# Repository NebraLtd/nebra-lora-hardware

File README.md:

# nebra-lora-hardware
Hardware Files for a variety of Nebra Lora Hardware

# Licenses

All hardware is licensed under Creative Commons Attribution Share Alike 4.0.

Software Snippets are licensed under the MIT License.

Copies of both can be found in the respective HARDWARE-LICENSE and SOFTWARE-LICENSE files.

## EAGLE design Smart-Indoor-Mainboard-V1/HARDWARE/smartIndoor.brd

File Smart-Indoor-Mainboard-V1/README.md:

# Nebra Smart Indoor Mainboard
Hardware Files for the mainboard used in the Nebra Helium Indoor Hotspot

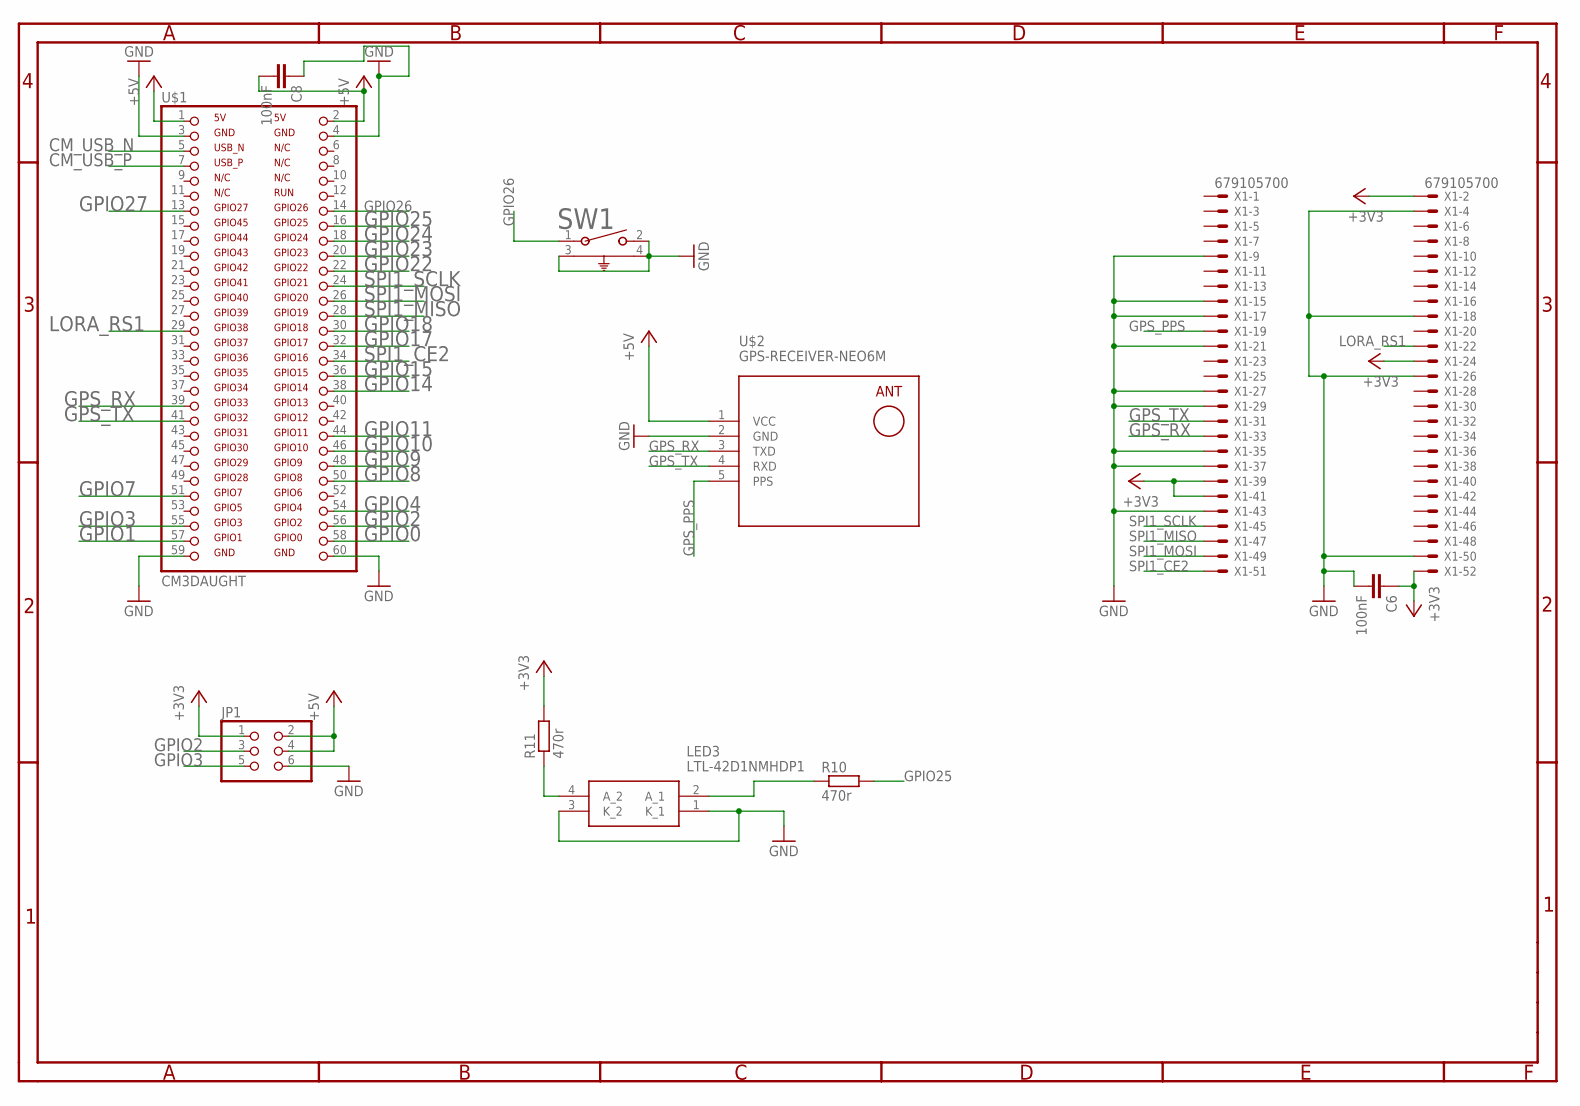
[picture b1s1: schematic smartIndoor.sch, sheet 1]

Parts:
C6, C8: 100nF; C0603
JP1: PINHD-2X3; 2X03
LED3: LTL-42D1NMHDP1; LTL42D1NMHDP1
R10, R11: 470r; R0603
SW1: 1825027-8; SW2_1825027-C_TEC
U$1: CM3DAUGHT; 2X30
U$2: GPS-RECEIVER-NEO6M
X1: 679105700

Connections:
+3V3: C6.1, JP1.1, R11.2, X1.2, X1.24, X1.39, X1.41, X1.52; also elsewhere on the board
+5V: C8.2, JP1.2, JP1.4, U$1.1 (5V), U$1.2 (5V), U$2.1 (VCC); also elsewhere on the board
CM_USB_N: U$1.5 (USB_N); also elsewhere on the board
CM_USB_P: U$1.7 (USB_P); also elsewhere on the board
GND: C6.2, C8.1, JP1.6, LED3.1 (K_1), LED3.3 (K_2), SW1.2, SW1.3, SW1.4, U$1.3 (GND), U$1.4 (GND), U$1.59 (GND), U$1.60 (GND), U$2.2 (GND), X1.4, X1.9, X1.15, X1.17, X1.18, X1.21, X1.26, X1.27, X1.29, X1.35, X1.37, X1.43, X1.50; also elsewhere on the board
GPIO0: U$1.58 (GPIO0)
GPIO1: U$1.57 (GPIO1)
GPIO2: JP1.3, U$1.56 (GPIO2)
GPIO3: JP1.5, U$1.55 (GPIO3)
GPIO4: U$1.54 (GPIO4)
GPIO7: U$1.51 (GPIO7)
GPIO8: U$1.50 (GPIO8)
GPIO9: U$1.48 (GPIO9)
GPIO10: U$1.46 (GPIO10)
GPIO11: U$1.44 (GPIO11)
GPIO14: U$1.38 (GPIO14)
GPIO15: U$1.36 (GPIO15)
GPIO17: U$1.32 (GPIO17)
GPIO18: U$1.30 (GPIO18)
GPIO22: U$1.22 (GPIO22)
GPIO23: U$1.20 (GPIO23)
GPIO24: U$1.18 (GPIO24)
GPIO25: R10.2, U$1.16 (GPIO25)
GPIO26: SW1.1, U$1.14 (GPIO26)
GPIO27: U$1.13 (GPIO27)
GPS_PPS: U$2.5 (PPS), X1.19
GPS_RX: U$1.39 (GPIO33), U$2.3 (TXD), X1.33
GPS_TX: U$1.41 (GPIO32), U$2.4 (RXD), X1.31
LORA_RS1: U$1.29 (GPIO38), X1.22
unnamed: LED3.4 (A_2), R11.1
unnamed: LED3.2 (A_1), R10.1
SPI1_CE2: U$1.34 (GPIO16), X1.51
SPI1_MISO: U$1.28 (GPIO19), X1.47
SPI1_MOSI: U$1.26 (GPIO20), X1.49
SPI1_SCLK: U$1.24 (GPIO21), X1.45

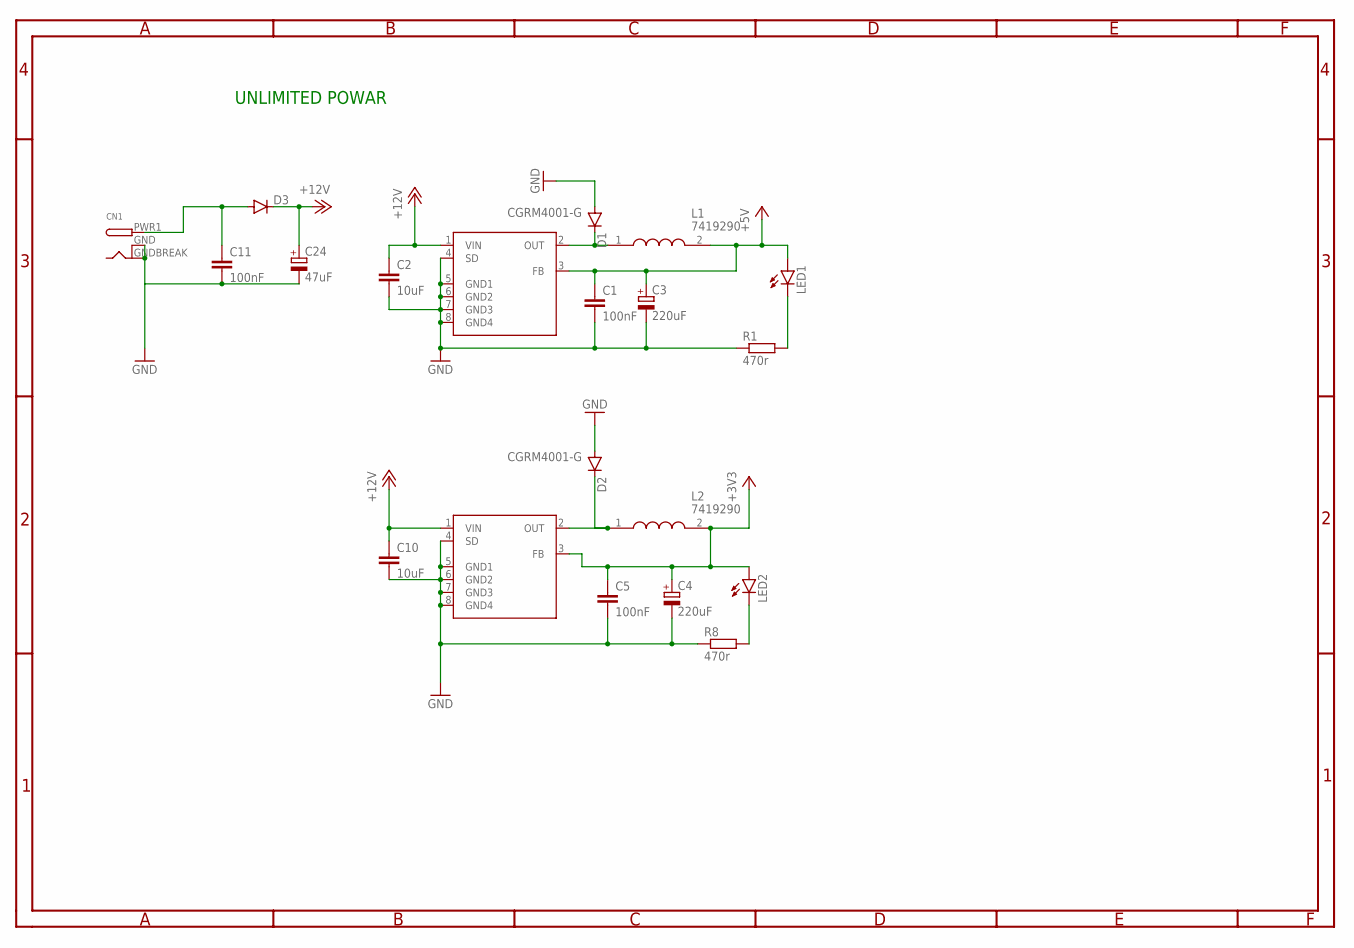
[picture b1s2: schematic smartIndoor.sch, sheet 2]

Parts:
C1, C5, C11: 100nF; C0603
C2, C10: 10uF; C0603
C3, C4: 220uF; PANASONIC_D
C24: 47uF; PANASONIC_D
CN1: DCBARRELSMT; DCJACK_2MM_SMT
D1, D2: CGRM4001-G; SOD-123_MINI-SMA
D3: DIODE-SMB; SMB
L1, L2: 7419290; INDPM115100X410N
LED1, LED2: LEDCHIP-LED0603; CHIP-LED0603
R1, R8: 470r; R0603
U1, U2: AP1509; SO08

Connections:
+3V3: C4.+, C5.1, L2.2, LED2.A, U2.3 (FB); also elsewhere on the board
+5V: C1.1, C3.+, L1.2, LED1.A, U1.3 (FB); also elsewhere on the board
+12V: C2.1, C10.1, C24.+, D3.C, U1.1 (VIN), U2.1 (VIN)
GND: C1.2, C2.2, C3.-, C4.-, C5.2, C10.2, C11.2, C24.-, CN1.GND (GNDBREAK), CN1.GNDBREAK (GND), D1.A, D2.A, R1.1, R8.1, U1.4 (SD), U1.5 (GND1), U1.6 (GND2), U1.7 (GND3), U1.8 (GND4), U2.4 (SD), U2.5 (GND1), U2.6 (GND2), U2.7 (GND3), U2.8 (GND4); also elsewhere on the board
unnamed: C11.1, CN1.PWR1 (PWR), D3.A
unnamed: LED1.C, R1.2
unnamed: D1.C, L1.1, U1.2 (OUT)
unnamed: LED2.C, R8.2
unnamed: D2.C, L2.1, U2.2 (OUT)

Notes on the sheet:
UNLIMITED POWAR

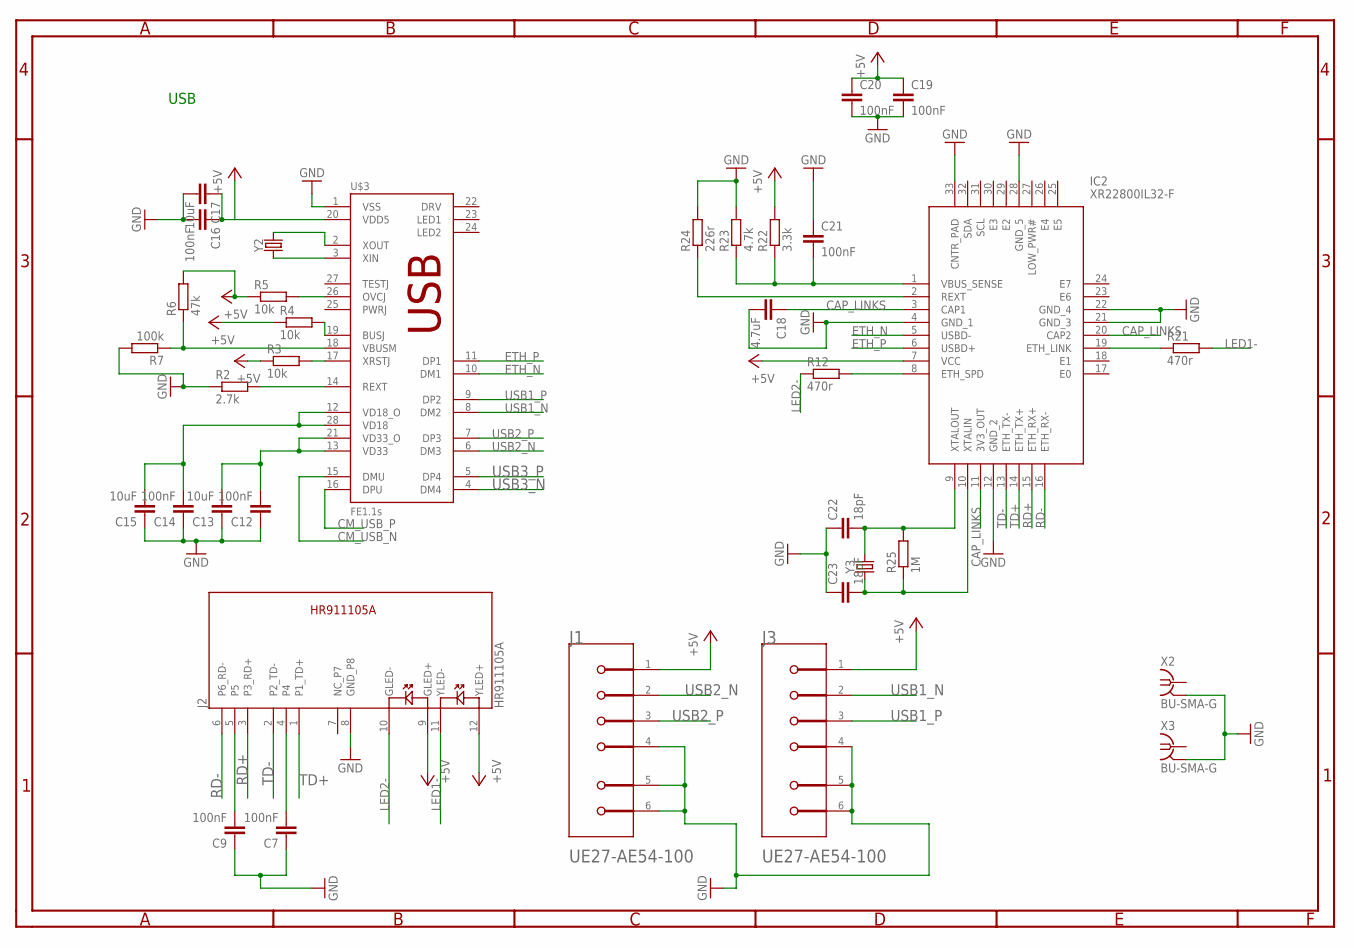
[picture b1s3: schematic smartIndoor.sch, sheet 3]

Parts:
C7, C9, C12, C14, C16, C19, C20, C21: 100nF; C0603
C13, C15, C17: 10uF; C0603
C18: 4.7uF; C0603
C22, C23: 18pF; C0603
IC2: XR22800IL32-F; QFN50P500X500X100-33N
J1, J3: AMPHENOL_UE27-AE54-100AMPHENOL_UE27-AE54-100_0_0; AMPHENOL_UE27-AE54-100_0
J2: HR911105A
R2: 2.7k; R0603
R3, R4, R5: 10k; R0603
R6: 47k; R0603
R7: 100k; R0603
R12, R21: 470r; R0603
R22: 3.3k; R0603
R23: 4.7k; R0603
R24: 226r; R0603
R25: 1M; R0603
U$3: FE1.1S; FE1.1S_SSOP-28
X2, X3: BU-SMA-G
Y2: 12mHZ; HC49UP
Y3: 25Mhz; HC49UP

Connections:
+5V: C16.1, C17.1, C19.1, C20.1, IC2.7 (VCC), J1.1, J2.9 (GLED+), J2.12 (YLED+), J3.1, R3.1, R4.1, R5.1, R6.2, R22.2, U$3.20 (VDD5); also elsewhere on the board
CAP_LINKS: C18.1, IC2.3 (CAP1), IC2.11 (3V3_OUT), IC2.20 (CAP2)
CM_USB_N: U$3.15 (DMU); also elsewhere on the board
CM_USB_P: U$3.16 (DPU); also elsewhere on the board
ETH_N: IC2.5 (USBD-), U$3.10 (DM1)
ETH_P: IC2.6 (USBD+), U$3.11 (DP1)
GND: C7.1, C9.1, C12.1, C13.1, C14.1, C15.1, C16.2, C17.2, C18.2, C19.2, C20.2, C21.1, C22.1, C23.1, IC2.4 (GND_1), IC2.12 (GND_2), IC2.21 (GND_3), IC2.22 (GND_4), IC2.28 (GND_5), IC2.33 (CNTR_PAD), J1.4, J1.5 (MNT_1), J1.6 (MNT_2), J2.8 (GND_P8), J3.4, J3.5 (MNT_1), J3.6 (MNT_2), R2.1, R7.2, R23.2, R24.2, U$3.1 (VSS), X2.2, X2.3 (2), X2.4 (2), X2.5 (2), X3.2, X3.3 (2), X3.4 (2), X3.5 (2); also elsewhere on the board
LED1-: J2.11 (YLED-), R21.2
LED2-: J2.10 (GLED-), R12.1
unnamed: C7.2, J2.4
unnamed: C9.2, J2.5
unnamed: C12.2, C13.2, U$3.13 (VD33), U$3.21 (VD33_O)
unnamed: C14.2, C15.2, U$3.12 (VD18_O), U$3.28 (VD18)
unnamed: R5.2, U$3.26 (OVCJ)
unnamed: R2.2, U$3.14 (REXT)
unnamed: R4.2, U$3.19 (BUSJ)
unnamed: R6.1, R7.1, U$3.18 (VBUSM)
unnamed: R3.2, U$3.17 (XRSTJ)
unnamed: U$3.2 (XOUT), Y2.2
unnamed: U$3.3 (XIN), Y2.1
unnamed: IC2.19 (ETH_LINK), R21.1
unnamed: C23.2, IC2.10 (XTALIN), R25.1, Y3.1
unnamed: C22.2, IC2.9 (XTALOUT), R25.2, Y3.2
unnamed: IC2.8 (ETH_SPD), R12.2
unnamed: IC2.2 (REXT), R24.1
unnamed: C21.2, IC2.1 (VBUS_SENSE), R22.1, R23.1
RD+: IC2.15 (ETH_RX+), J2.3 (P3_RD+)
RD-: IC2.16 (ETH_RX-), J2.6 (P6_RD-)
TD+: IC2.14 (ETH_TX+), J2.1 (P1_TD+)
TD-: IC2.13 (ETH_TX-), J2.2 (P2_TD-)
USB1_N: J3.2, U$3.8 (DM2)
USB1_P: J3.3, U$3.9 (DP2)
USB2_N: J1.2, U$3.6 (DM3)
USB2_P: J1.3, U$3.7 (DP3)
USB3_N: U$3.4 (DM4)
USB3_P: U$3.5 (DP4)

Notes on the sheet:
USB

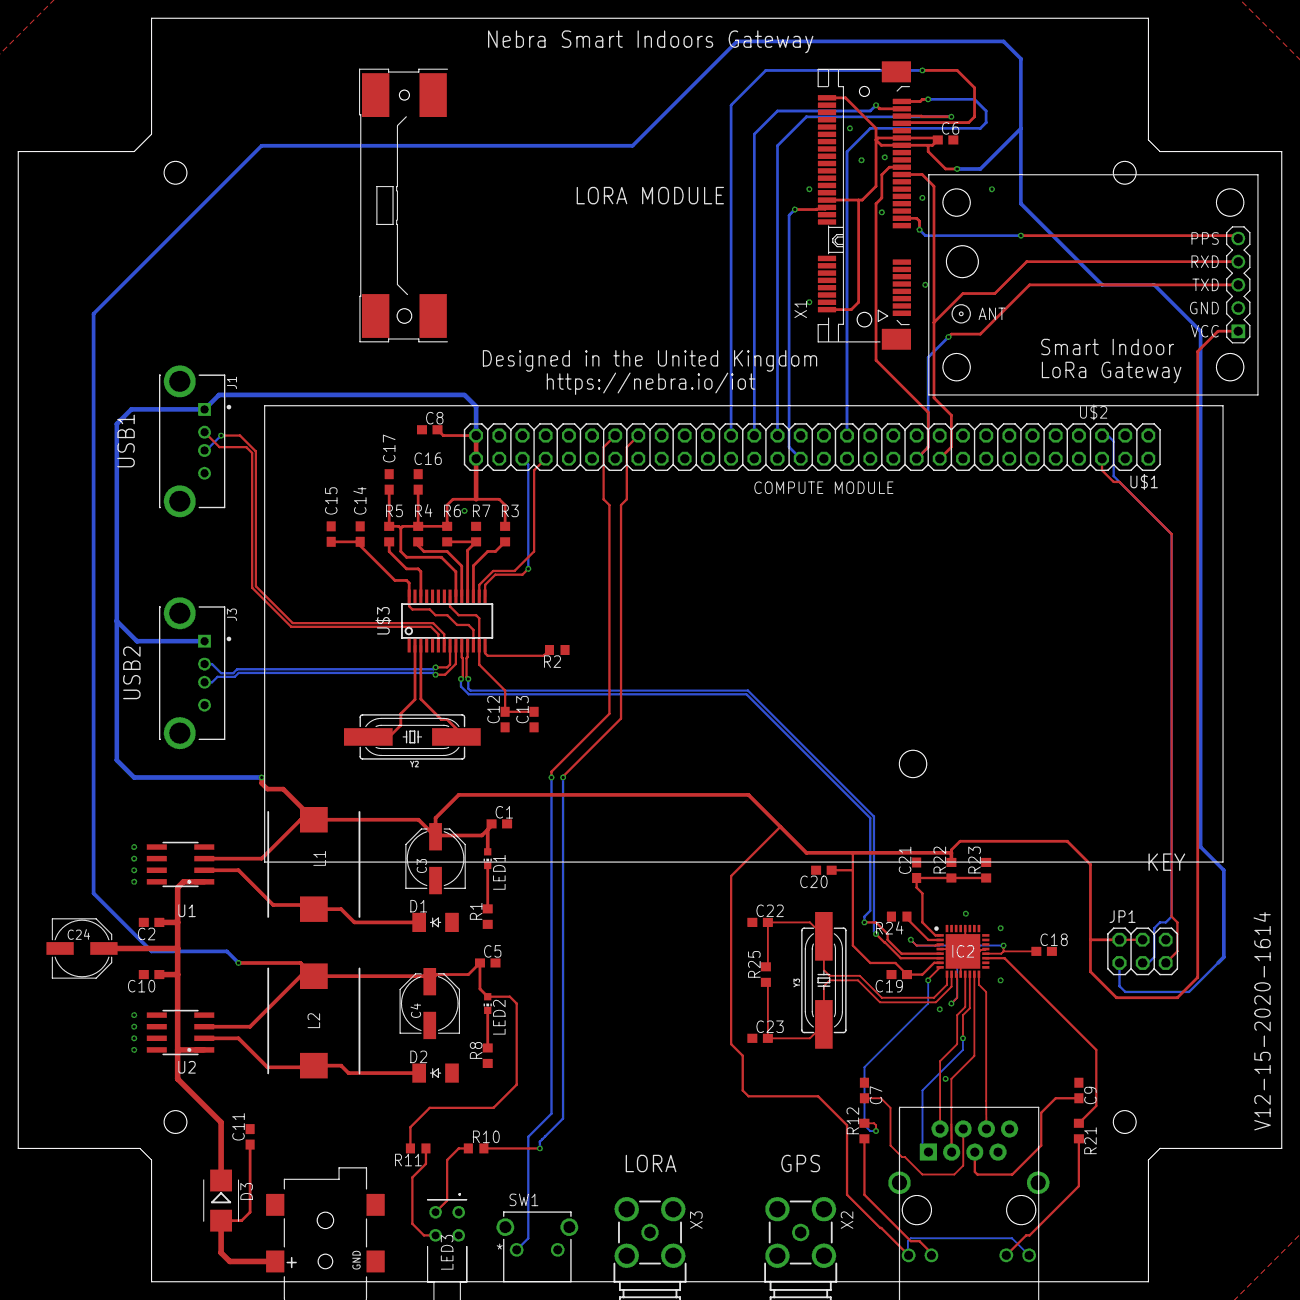
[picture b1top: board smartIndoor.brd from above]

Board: 2 copper layers, 138.4 x 138.4 mm, 65 parts (0 on the bottom side), 55 nets.

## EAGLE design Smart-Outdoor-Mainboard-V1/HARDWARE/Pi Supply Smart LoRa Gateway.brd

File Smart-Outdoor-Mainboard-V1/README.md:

# Nebra Smart Outdoor Mainboard
Hardware Files for the mainboard used in the Nebra Helium Outdoor Hotspot

The Nebra Smart Outdoor Mainboard contains the following features:

* 9-16V DC Power Input
* 48V 802.3AF POE Support
* 10/100 USB Networking
* Built in USB Hub connected to USB Port, Networking & m-pcie slot.
* "Raspberry Pi" Header - 40 Pin RPi style header, please note only the first 24 pins are wired
* M-PCIE Slot (USB Only) with circuitry to use a 3G/4G Module
* Dual slots for LoRa modules, wired to separate SPI Bus.
* GPS Module

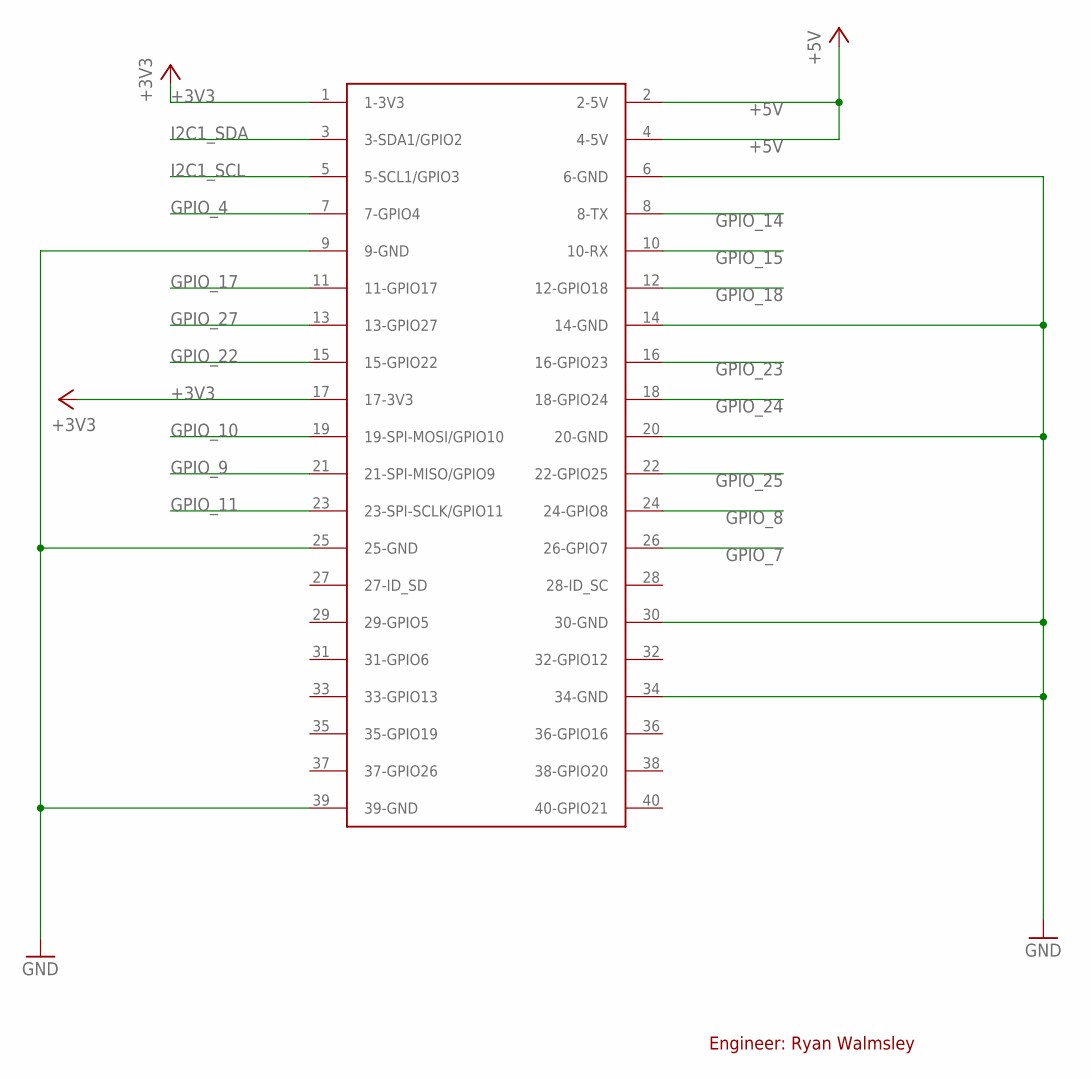
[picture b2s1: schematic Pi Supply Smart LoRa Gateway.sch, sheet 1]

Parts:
U$5: RASPBERRY-PI+NONOTCHES; RASPBERRY-PI-PLUS

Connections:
+3V3: U$5.1 (1-3V3), U$5.17 (17-3V3); also elsewhere on the board
+5V: U$5.2 (2-5V), U$5.4 (4-5V); also elsewhere on the board
GND: U$5.6 (6-GND), U$5.9 (9-GND), U$5.14 (14-GND), U$5.20 (20-GND), U$5.25 (25-GND), U$5.30 (30-GND), U$5.34 (34-GND), U$5.39 (39-GND); also elsewhere on the board
GPIO_4: U$5.7 (7-GPIO4); also elsewhere on the board
GPIO_7: U$5.26 (26-GPIO7)
GPIO_8: U$5.24 (24-GPIO8); also elsewhere on the board
GPIO_9: U$5.21 (21-SPI-MISO/GPIO9); also elsewhere on the board
GPIO_10: U$5.19 (19-SPI-MOSI/GPIO10); also elsewhere on the board
GPIO_11: U$5.23 (23-SPI-SCLK/GPIO11); also elsewhere on the board
GPIO_14: U$5.8 (8-TX); also elsewhere on the board
GPIO_15: U$5.10 (10-RX); also elsewhere on the board
GPIO_17: U$5.11 (11-GPIO17); also elsewhere on the board
GPIO_18: U$5.12 (12-GPIO18); also elsewhere on the board
GPIO_22: U$5.15 (15-GPIO22); also elsewhere on the board
GPIO_23: U$5.16 (16-GPIO23); also elsewhere on the board
GPIO_24: U$5.18 (18-GPIO24); also elsewhere on the board
GPIO_25: U$5.22 (22-GPIO25); also elsewhere on the board
GPIO_27: U$5.13 (13-GPIO27); also elsewhere on the board
I2C1_SCL: U$5.5 (5-SCL1/GPIO3); also elsewhere on the board
I2C1_SDA: U$5.3 (3-SDA1/GPIO2); also elsewhere on the board

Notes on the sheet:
Engineer: Ryan Walmsley

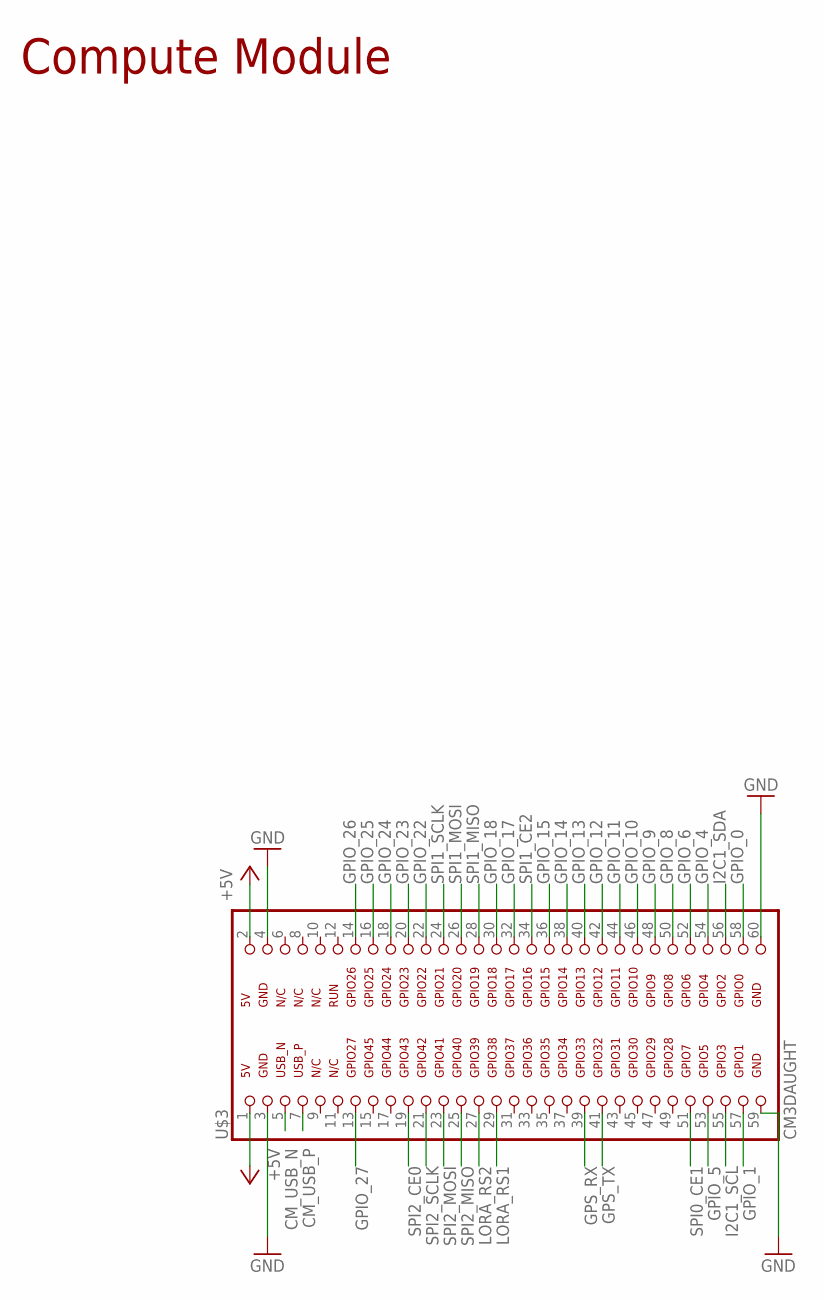
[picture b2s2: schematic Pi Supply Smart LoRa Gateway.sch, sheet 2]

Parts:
U$3: CM3DAUGHT; 2X30

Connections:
+5V: U$3.1 (5V), U$3.2 (5V); also elsewhere on the board
CM_USB_N: U$3.5 (USB_N); also elsewhere on the board
CM_USB_P: U$3.7 (USB_P); also elsewhere on the board
GND: U$3.3 (GND), U$3.4 (GND), U$3.59 (GND), U$3.60 (GND); also elsewhere on the board
GPIO_0: U$3.58 (GPIO0)
GPIO_1: U$3.57 (GPIO1)
GPIO_4: U$3.54 (GPIO4); also elsewhere on the board
GPIO_5: U$3.53 (GPIO5)
GPIO_6: U$3.52 (GPIO6)
GPIO_8: U$3.50 (GPIO8); also elsewhere on the board
GPIO_9: U$3.48 (GPIO9); also elsewhere on the board
GPIO_10: U$3.46 (GPIO10); also elsewhere on the board
GPIO_11: U$3.44 (GPIO11); also elsewhere on the board
GPIO_12: U$3.42 (GPIO12)
GPIO_13: U$3.40 (GPIO13)
GPIO_14: U$3.38 (GPIO14); also elsewhere on the board
GPIO_15: U$3.36 (GPIO15); also elsewhere on the board
GPIO_17: U$3.32 (GPIO17); also elsewhere on the board
GPIO_18: U$3.30 (GPIO18); also elsewhere on the board
GPIO_22: U$3.22 (GPIO22); also elsewhere on the board
GPIO_23: U$3.20 (GPIO23); also elsewhere on the board
GPIO_24: U$3.18 (GPIO24); also elsewhere on the board
GPIO_25: U$3.16 (GPIO25); also elsewhere on the board
GPIO_26: U$3.14 (GPIO26)
GPIO_27: U$3.13 (GPIO27); also elsewhere on the board
GPS_RX: U$3.39 (GPIO33); also elsewhere on the board
GPS_TX: U$3.41 (GPIO32); also elsewhere on the board
I2C1_SCL: U$3.55 (GPIO3); also elsewhere on the board
I2C1_SDA: U$3.56 (GPIO2); also elsewhere on the board
LORA_RS1: U$3.29 (GPIO38); also elsewhere on the board
LORA_RS2: U$3.27 (GPIO39); also elsewhere on the board
SPI0_CE1: U$3.51 (GPIO7)
SPI1_CE2: U$3.34 (GPIO16); also elsewhere on the board
SPI1_MISO: U$3.28 (GPIO19); also elsewhere on the board
SPI1_MOSI: U$3.26 (GPIO20); also elsewhere on the board
SPI1_SCLK: U$3.24 (GPIO21); also elsewhere on the board
SPI2_CE0: U$3.19 (GPIO43); also elsewhere on the board
SPI2_MISO: U$3.25 (GPIO40); also elsewhere on the board
SPI2_MOSI: U$3.23 (GPIO41); also elsewhere on the board
SPI2_SCLK: U$3.21 (GPIO42); also elsewhere on the board

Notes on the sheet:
Compute Module

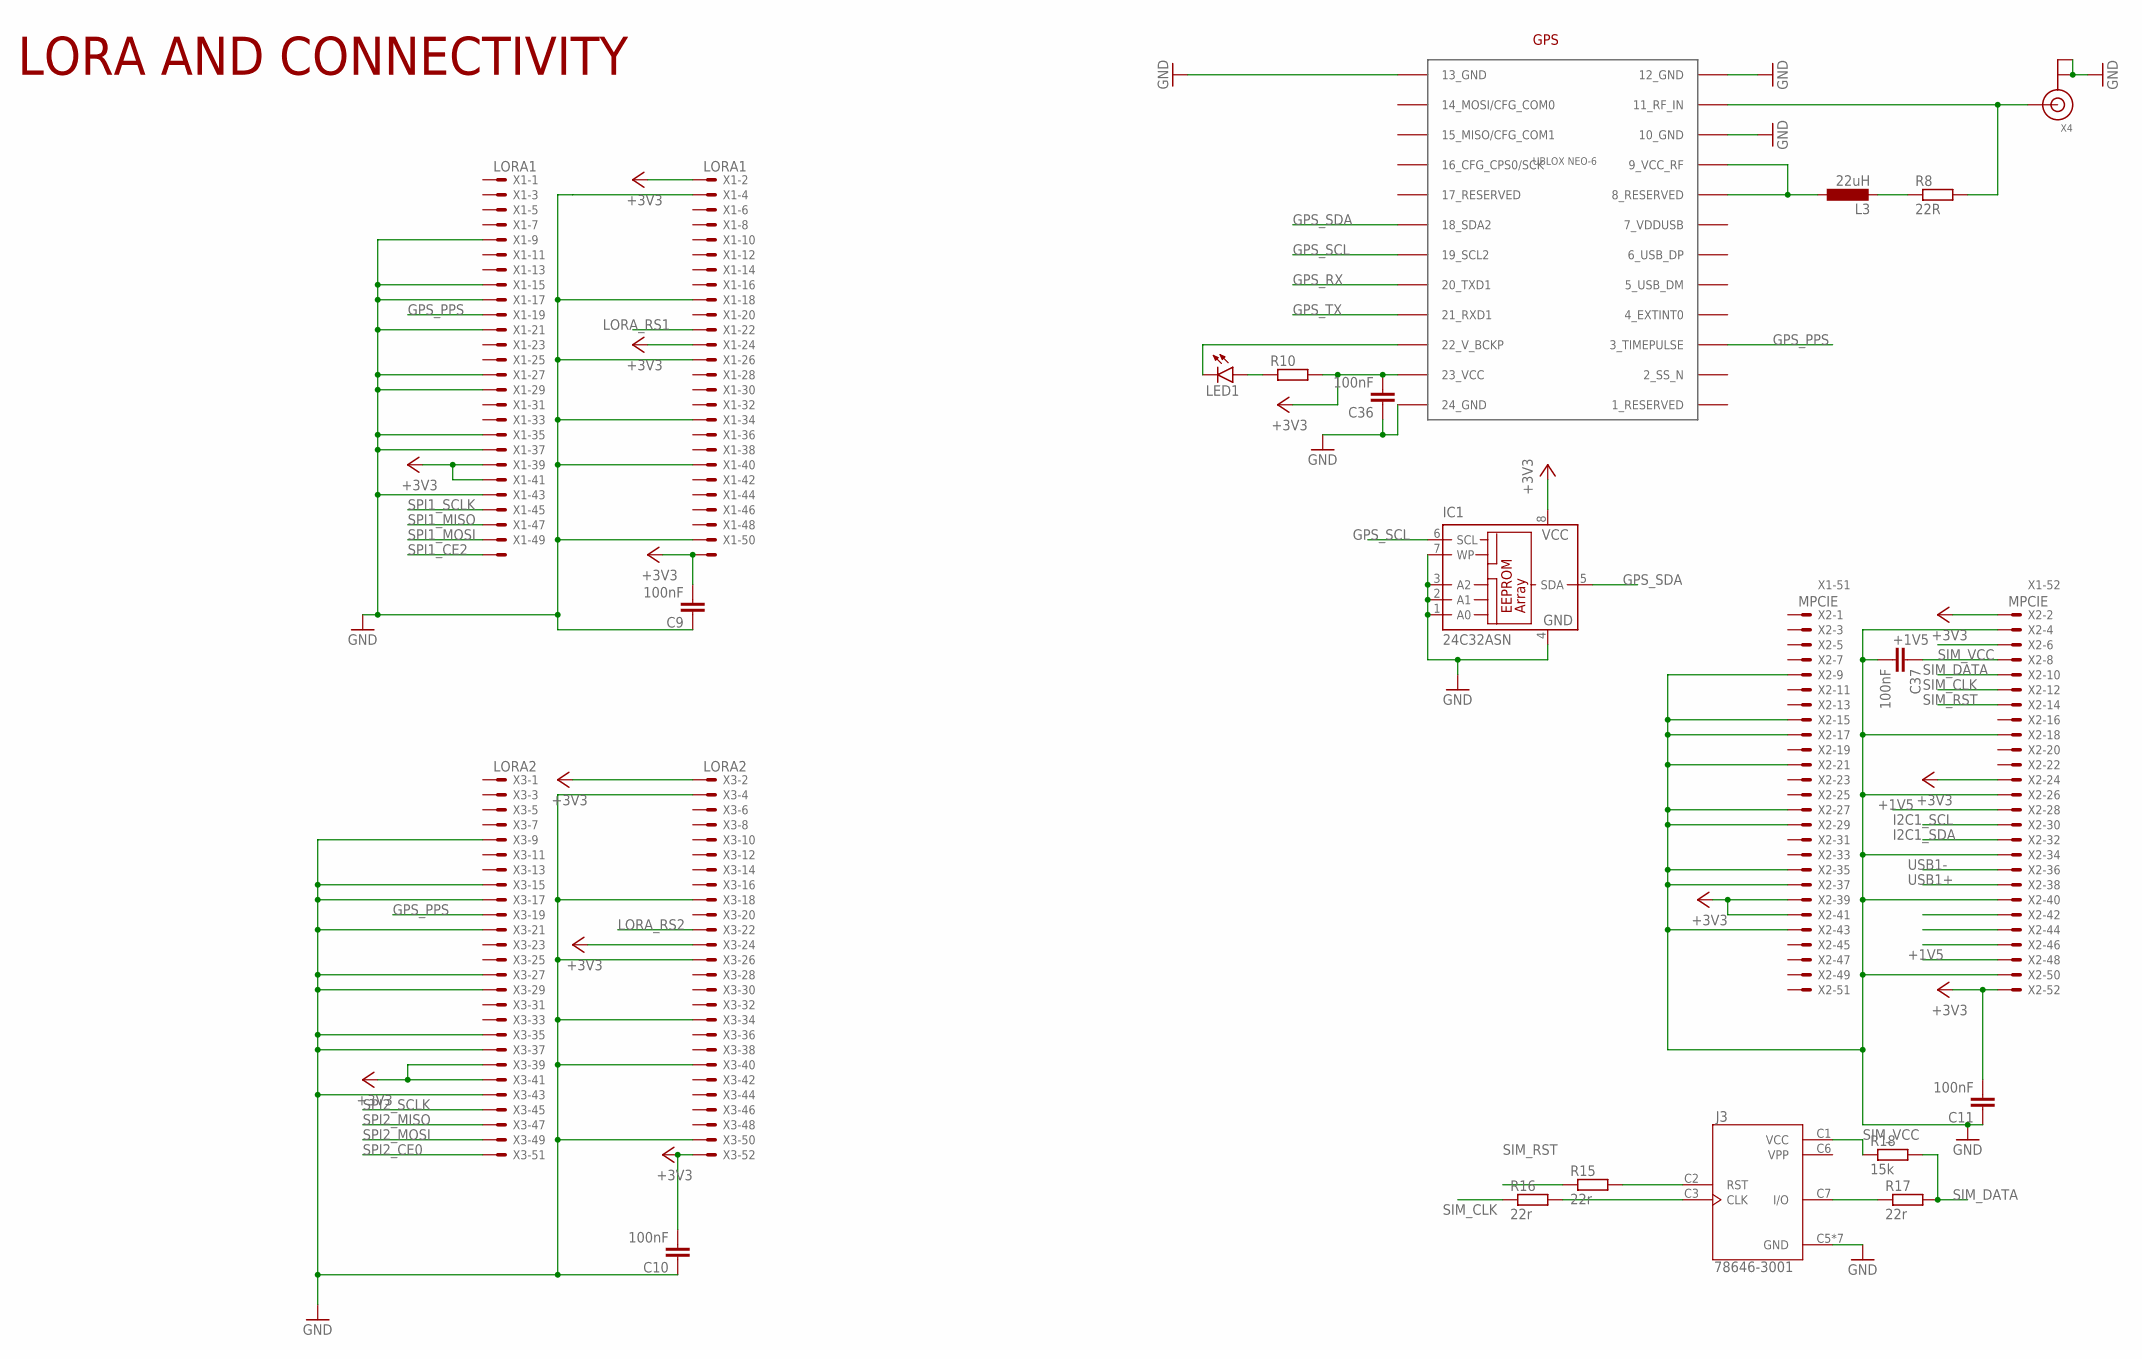
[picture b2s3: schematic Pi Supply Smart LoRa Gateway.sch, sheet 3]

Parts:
C9, C10, C11, C36, C37: 100nF; C0603
IC1: 24C32ASN; SO-08
J3: 78646-3001; CONN_78646-3001
L3: 22uH; L2012C
LED1: LEDCHIPLED_0603; CHIPLED_0603
R8: 22R; R0603
R10: R-EU_R0603; R0603
R15, R16, R17: 22r; R0603
R18: 15k; R0603
U$4: UBLOX_NEO-6; UBLOX_NEO-6P
X1: LORA1; 679105700
X2: MPCIE; 679105700
X3: LORA2; 679105700
X4: ANTENNA_U.FL; U.FL

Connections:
+1V5: X2.6, X2.28, X2.48; also elsewhere on the board
+3V3: C9.2, C10.2, C11.2, C36.2, IC1.8 (VCC), R10.2, U$4.23_VCC, X1.2, X1.24, X1.39, X1.41, X1.52, X2.2, X2.24, X2.39, X2.41, X2.52, X3.2, X3.24, X3.39, X3.41, X3.52; also elsewhere on the board
GND: C9.1, C10.1, C11.1, C36.1, C37.2, IC1.1 (A0), IC1.2 (A1), IC1.3 (A2), IC1.4 (GND), IC1.7 (WP), J3.C5 (GND), J3.G1 (GND), J3.G2 (GND), J3.G3 (GND), J3.G4 (GND), J3.G5 (GND), J3.G6 (GND), U$4.10_GND, U$4.12_GND, U$4.13_GND, U$4.24_GND, X1.4, X1.9, X1.15, X1.17, X1.18, X1.21, X1.26, X1.27, X1.29, X1.34, X1.35, X1.37, X1.40, X1.43, X1.50, X2.4, X2.9, X2.15, X2.17, X2.18, X2.21, X2.26, X2.27, X2.29, X2.34, X2.35, X2.37, X2.40, X2.43, X2.50, X3.4, X3.9, X3.15, X3.17, X3.18, X3.21, X3.26, X3.27, X3.29, X3.34, X3.35, X3.37, X3.40, X3.43, X3.50, X4.1 (GND), X4.2 (GND); also elsewhere on the board
GPS_PPS: U$4.3_TIMEPULSE, X1.19, X3.19
GPS_RX: U$4.20_TXD1; also elsewhere on the board
GPS_SCL: IC1.6 (SCL), U$4.19_SCL2
GPS_SDA: IC1.5 (SDA), U$4.18_SDA2
GPS_TX: U$4.21_RXD1; also elsewhere on the board
I2C1_SCL: X2.30; also elsewhere on the board
I2C1_SDA: X2.32; also elsewhere on the board
LORA_RS1: X1.22; also elsewhere on the board
LORA_RS2: X3.22; also elsewhere on the board
unnamed: L3.1, U$4.8_RESERVED, U$4.9_VCC_RF
unnamed: LED1.C, U$4.22_V_BCKP
unnamed: J3.C7 (I/O), R17.1
unnamed: J3.C2 (RST), R15.2
unnamed: J3.C3 (CLK), R16.2
unnamed: L3.2, R8.1
unnamed: R8.2, U$4.11_RF_IN, X4.3 (SIGNAL)
unnamed: LED1.A, R10.1
SIM_CLK: R16.1, X2.12
SIM_DATA: R17.2, R18.2, X2.10
SIM_RST: R15.1, X2.14
SIM_VCC: C37.1, J3.C1 (VCC), R18.1, X2.8
SPI1_CE2: X1.51; also elsewhere on the board
SPI1_MISO: X1.47; also elsewhere on the board
SPI1_MOSI: X1.49; also elsewhere on the board
SPI1_SCLK: X1.45; also elsewhere on the board
SPI2_CE0: X3.51; also elsewhere on the board
SPI2_MISO: X3.47; also elsewhere on the board
SPI2_MOSI: X3.49; also elsewhere on the board
SPI2_SCLK: X3.45; also elsewhere on the board
USB1+: X2.38; also elsewhere on the board
USB1-: X2.36; also elsewhere on the board
VPP: J3.C6 (VPP)

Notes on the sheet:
LORA AND CONNECTIVITY
GPS

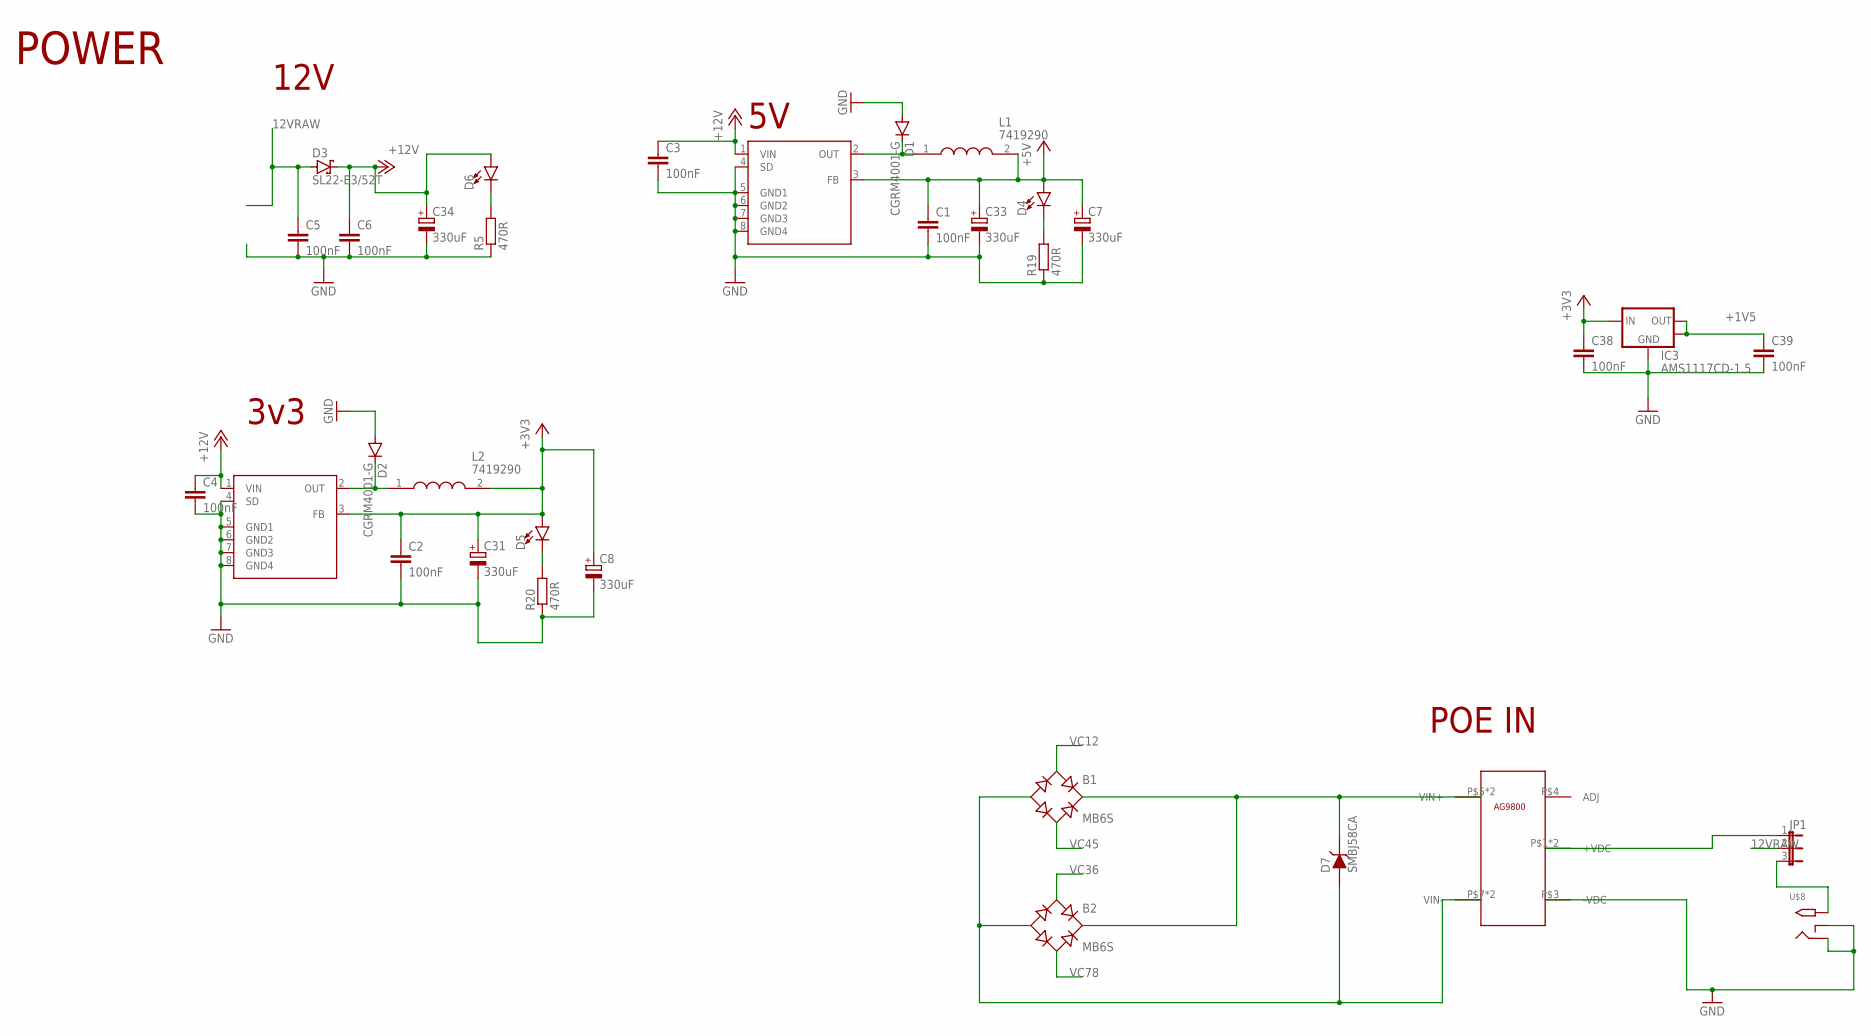
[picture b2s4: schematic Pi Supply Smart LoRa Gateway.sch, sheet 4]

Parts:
B1, B2: MB6S; SOIC-4
C1, C2, C3, C4, C5, C6, C38, C39: 100nF; C0603
C7, C8, C31, C33, C34: 330uF; PANASONIC_E
D1, D2: CGRM4001-G; SOD-123_MINI-SMA
D3: SL22-E3/52T; SMB
D4, D5, D6: LED0603; LED-0603
D7: SMBJ58CA; DO-214AA
IC3: AMS1117CD-1.5; SOT-223-3
JP1: JP2E; JP2
L1, L2: 7419290; INDPM115100X410N
R5, R19, R20: 470R; R0603
U1: AP1509; SO08
U2: AP1509-50; SO08
U$1: AG9800
U$8: 2.1MMJACKSMT; DCJACK_2MM_SMT

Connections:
12VRAW: C5.1, D3.A, JP1.2
+1V5: C39.1, IC3.2 (VOUT), IC3.4 (HEATSINK); also elsewhere on the board
+3V3: C2.1, C8.+, C31.+, C38.1, D5.A, IC3.3 (VIN), L2.2, U1.3 (FB); also elsewhere on the board
+5V: C1.1, C7.+, C33.+, D4.A, L1.2, U2.3 (FB); also elsewhere on the board
+12V: C3.1, C4.1, C6.1, C34.+, D3.C, D6.A, U1.1 (VIN), U2.1 (VIN)
GND: C1.2, C2.2, C3.2, C4.2, C5.2, C6.2, C7.-, C8.-, C31.-, C33.-, C34.-, C38.2, C39.2, D1.A, D2.A, IC3.1 (GND), R5.1, R19.1, R20.1, U1.4 (SD), U1.5 (GND1), U1.6 (GND2), U1.7 (GND3), U1.8 (GND4), U2.4 (SD), U2.5 (GND1), U2.6 (GND2), U2.7 (GND3), U2.8 (GND4), U$1.P$3 (-VDC), U$8.GND (RING), U$8.GNDBREAK (RING_SW); also elsewhere on the board
unnamed: JP1.1, U$1.P$1 (+VDC), U$1.P$2 (+VDC)
unnamed: D1.C, L1.1, U2.2 (OUT)
unnamed: JP1.3, U$8.PWR2 (TIP)
unnamed: D2.C, L2.1, U1.2 (OUT)
unnamed: D6.C, R5.2
unnamed: D4.C, R19.2
unnamed: D5.C, R20.2
POEVIN+: B1.+, B2.+, D7.P$1 (C), U$1.P$5 (VIN+), U$1.P$6 (VIN+)
POEVIN-: B1.-, B2.-, D7.P$2 (A), U$1.P$7 (VIN-), U$1.P$8 (VIN-)
VC12: B1.~1 (AC1); also elsewhere on the board
VC36: B2.~1 (AC1); also elsewhere on the board
VC45: B1.~2 (AC2); also elsewhere on the board
VC78: B2.~2 (AC2); also elsewhere on the board

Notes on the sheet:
POWER
3v3
POE IN
12V

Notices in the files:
parts and their libraries:
SparkFun-Clocks: Licensing: Creative Commons ShareAlike 4.0 International - https://creativecommons.org/licenses/by-sa/4.0
pimoroni: Licensing: CC v3.0 Share-Alike You are welcome to use this library for commercial purposes.
dframes: Copyright (C) 2004, Bob Starr (bobstarr@mindspring.com)
